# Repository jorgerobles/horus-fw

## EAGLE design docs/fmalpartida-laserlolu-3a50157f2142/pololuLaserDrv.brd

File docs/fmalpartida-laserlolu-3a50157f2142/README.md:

# laserlolu - pololu laser driver adaptor #

## Over view ##
laserlolu is a small laser driver module that plugs into a pololu stepper driver socket. It uses the step and dir pins to switch the laser drivers.
It can handle 2 lasers up to 200mA each.

Eagle CAD sources available in the project source section.

## License ##
Released under the Creative Commons Attribution Share-Alike 3.0 License
http://creativecommons.org/licenses/by-sa/3.0
CC SA-BY

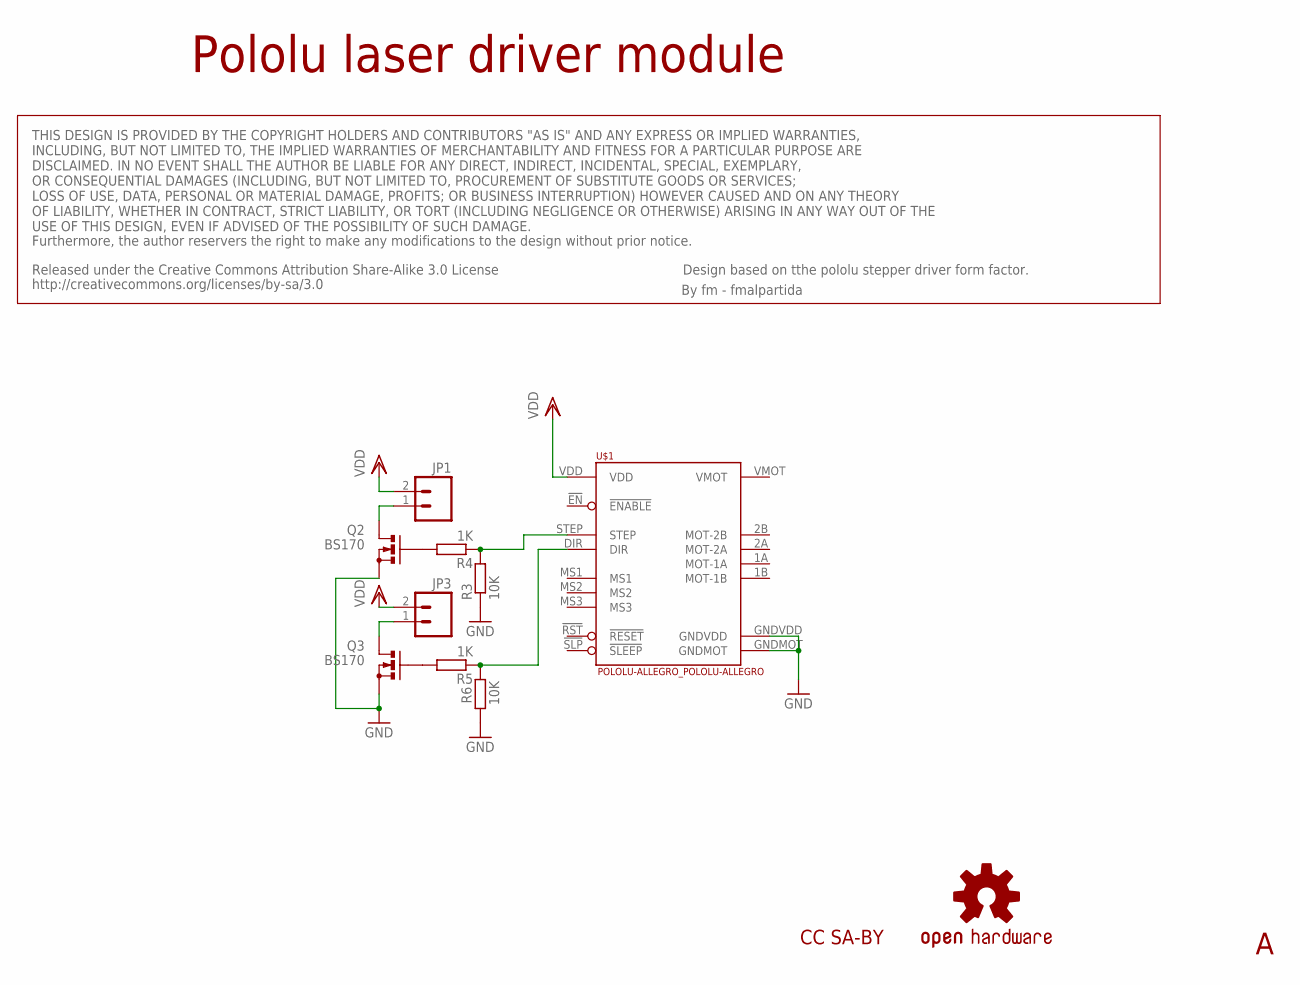
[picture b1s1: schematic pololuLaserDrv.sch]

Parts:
JP1, JP3: M02PTH; 1X02
Q2, Q3: BS170; SOT54E
R3, R6: 10K; 0204/5
R4, R5: 1K; 0204/5
U$1: POLOLU-ALLEGRO_POLOLU-ALLEGRO; POLOLU-ALLEGRO_POLOLU-ALLEGRO-PTH
U$2: OSHW-LOGOS; OSHW-LOGO-S

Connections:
GND: Q2.S, Q3.S, R3.1, R6.2, U$1.GNDMOT, U$1.GNDVDD
MOT-1A: U$1.1A (MOT-1A)
MOT-1B: U$1.1B (MOT-1B)
MOT-2A: U$1.2A (MOT-2A)
MOT-2B: U$1.2B (MOT-2B)
unnamed: Q2.G, R4.2
unnamed: R3.2, R4.1, U$1.STEP
unnamed: Q3.G, R5.2
unnamed: R5.1, R6.1, U$1.DIR
unnamed: JP1.1, Q2.D
unnamed: JP3.1, Q3.D
VDD: JP1.2, JP3.2, U$1.VDD
VMOT: U$1.VMOT

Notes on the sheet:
CC SA-BY
Pololu laser driver module
Released under the Creative Commons Attribution Share-Alike 3.0 License
http://creativecommons.org/licenses/by-sa/3.0
Design based on tthe pololu stepper driver form factor.
By fm - fmalpartida
THIS DESIGN IS PROVIDED BY THE COPYRIGHT HOLDERS AND CONTRIBUTORS "AS IS" AND ANY EXPRESS OR IMPLIED WARRANTIES, INCLUDING, BUT NOT LIMITED TO, THE IMPLIED WARRANTIES OF MERCHANTABILITY AND FITNESS FOR A PARTICULAR PURPOSE ARE DISCLAIMED. IN NO EVENT SHALL THE AUTHOR BE LIABLE FOR ANY DIRECT, INDIR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
Furthermore, the author reservers the right to make any modifications to the design without prior notice.

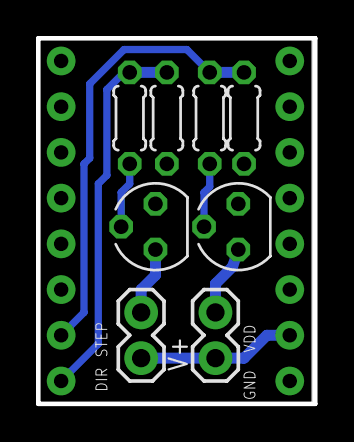
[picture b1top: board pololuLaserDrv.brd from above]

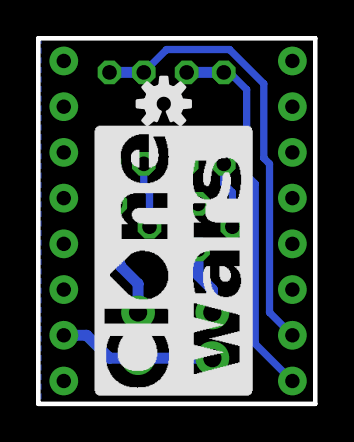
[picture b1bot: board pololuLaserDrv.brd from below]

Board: 2 copper layers, 15.4 x 20.3 mm, 11 parts (2 on the bottom side), 8 nets.

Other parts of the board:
U$3: CLONE_WARS

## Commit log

2015-02-10 @VincentM CNCV3 pin map
2015-02-15 VincentM Laserlolu para placa perforada
2015-02-15 Clon FMalpartida Laserlolu

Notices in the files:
parts and their libraries:
SparkFun: Licensing: CC v3.0 Share-Alike You are welcome to use this library for commercial purposes.
